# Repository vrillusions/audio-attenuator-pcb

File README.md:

# Audio Attenuator PCB

## Overview

Primarily was interested in designing a custom PCB for the first time.  This is a pretty basic circuit that attenuates or reduces the volume.  Reason for a static value vs one of those inline volume control knobs is the cheap ones tend to introduce static in to audio when adjusting the dial.  Also stereo separation can sometimes start to offset where one side is louder than the other.

This is primarily designed to handle the scenario where you have line level output and you need to feed it in to an input that takes mic level audio.  Using the given values will give a 10:1 reduction in power which corresponds to 20 db reduction in audio.  This is the least it will reduce the audio.  In reality the output impedance also plays a role.  For example if you have an output impedance of 1000 Ohm, that adds to the 1k Ohm resistor meaning it becomes 2k and 100.  Which gives you about a 30 db reduction in audio.  In the situation of a really hot line level audio needing to feed a mic input that still works fine.  If you're interested in learning more [this](https://diyaudioheaven.wordpress.com/tutorials/power-impedance-etc/) has a pretty good summary of what's all happening.

## Requirements

### Building it

- `R1` and `R2` are the larger of the two resistor values.  Recommend 1k ohm 1/4 watt 1% and then match them to find two as close together as possible
- `R3` and `R4` are the smaller of the two resistor values.  Recommend 100 ohm 1/4 watt 1% and then match them to find two as close together as possible
- `J1` and `J2` are based off the audio jacks I found on amazon.  Take note that a few have same footprint but pins are arranged differently.  Should have one in middle towards front and 4 along back.  Only the two outer pins are used.  Below are links to actual component used including the alternate 4 pin and 3 pin versions
    - [CUI SJ1-3525N](https://www.digikey.com/en/products/detail/cui-devices/SJ1-3525N/738687) - 5 pin version.  The extra pins are commonly used amps and such where if nothing is plugged in to jack then audio will pass through and come out via RCA jacks or something but then when you plug headphones in it will disconnect the path to RCA jacks and send audio to headphones.  Gives more flexibility to buy some extra to use in other circuits and only a couple cents more.
    - [CUI SJ1-3524N](https://www.digikey.com/en/products/detail/cui-devices/SJ1-3524N/738688) - 4 pin version
    - [CUI SJ1-3523N](https://www.digikey.com/en/products/detail/cui-devices/SJ1-3523N/738689) - 3 pin version.  Least expensive of the three and should work for most otehr circuits out there.

### PCB

- May make use of [DigiKey KiCad Library](https://github.com/Digi-Key/digikey-kicad-library)

## Usage

This is essentially a voltage divider circuit.  The effective reduction is based on the ratio of the two resistor values chosen along with the devices being used for the output and input.  In trial circuits this was 470ohm for `R1` and `R2` and 47ohm for `R3` and `R4`.  This should yield a 10:1 ratio reduction in power which corresponds to 20 db reduction in audio.  When testing with white noise output from computer and in to a tascam dr-07x receiver it showed about a 30 db reduction.  Which would be fine in my case where the tascam only records at mic level input and I need it to handle line level input from a DJ mixer which is commonly being driven to +10db or more.  I then swapped to 1k and 100 ohm resistors as they are far more common in packs of resistors.

## Changelog

### 2 - 2021-09-25

- re-arrange things to be more uniform
- shorten it slightly (Save $0.25! )
- widen the trace size
- makes use of a ground plane
- add some fancy labels
- label the resistors with actual values for most common scenario

### 1 - 2021-09-05

- Initial design

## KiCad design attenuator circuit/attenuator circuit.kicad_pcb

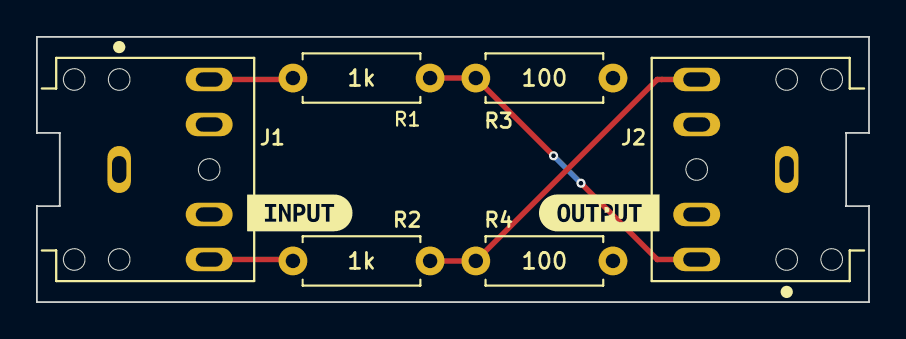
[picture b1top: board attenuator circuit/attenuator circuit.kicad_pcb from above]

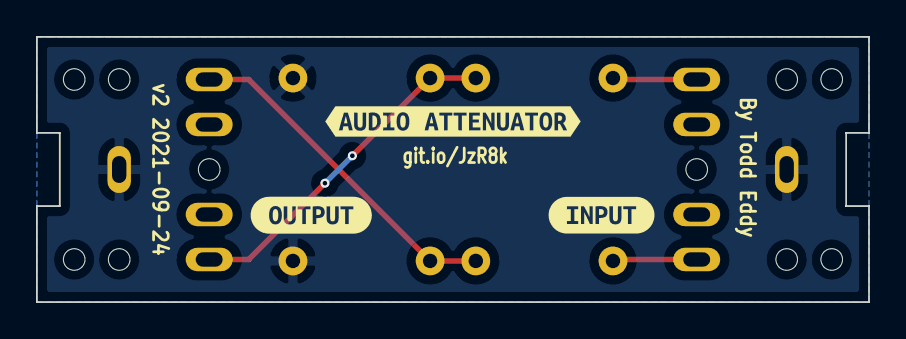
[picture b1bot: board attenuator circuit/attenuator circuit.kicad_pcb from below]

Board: 2 copper layers, 46.2 x 14.7 mm, 11 parts (3 on the bottom side), 5 nets.

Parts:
J1: INPUT; CUI_SJ1-3525N
J2: OUTPUT; CUI_SJ1-3525N
R1, R2: 1k; R_Axial_DIN0207_L6.3mm_D2.5mm_P7.62mm_Horizontal
R3, R4: 100; R_Axial_DIN0207_L6.3mm_D2.5mm_P7.62mm_Horizontal
kibuzzard-614ACF93, kibuzzard-614AD03C, kibuzzard-614AD37E, kibuzzard-614AD392, kibuzzard-614ADC34: G***; label

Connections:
/GND: J1.1, J2.1, R3.1, R4.2
unnamed: J1.2, R2.2
unnamed: J1.3, R1.2
unnamed: J2.2, R2.1, R4.1
unnamed: J2.3, R1.1, R3.2

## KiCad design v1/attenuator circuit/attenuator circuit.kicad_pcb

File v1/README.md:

## Overview

- version: 1
- created: September 5, 2021
- verified final PCB: NO

## Changelog

### 1 - 2021-09-05

- Initial design

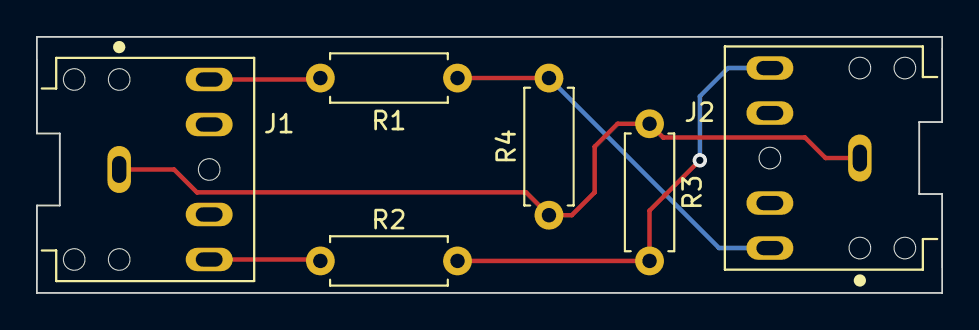
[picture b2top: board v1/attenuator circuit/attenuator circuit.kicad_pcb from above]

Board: 2 copper layers, 50.3 x 14.2 mm, 6 parts (0 on the bottom side), 5 nets.

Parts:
J1, J2: SJ1-3525N; CUI_SJ1-3525N
R1, R2: 42; R_Axial_DIN0207_L6.3mm_D2.5mm_P7.62mm_Horizontal
R3, R4: 420; R_Axial_DIN0207_L6.3mm_D2.5mm_P7.62mm_Horizontal

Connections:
unnamed: J1.1, J2.1, R3.1, R4.1
unnamed: J1.2, R2.2
unnamed: J1.3, R1.2
unnamed: J2.2, R2.1, R3.2
unnamed: J2.3, R1.1, R4.2

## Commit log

2021-09-06 Add initial template files
2021-09-06 Add v1 of attenuator circuit
2021-09-06 Update readme with specifics on parts to use
2021-09-18 Don't use individual subfolders for each version
    The GIT Way (tm) is to use tags
2021-09-25 Version 2 of PCB
    - re-arrange things to be more uniform
    - shorten it slightly (Save $0.25! )
    - widen the trace size
    - makes use of a ground plane
    - add some fancy labels
    - label the resistors with actual values for most common scenario
